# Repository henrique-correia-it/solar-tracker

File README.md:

# Dual-Axis IoT Solar Tracker

**Bare-metal ATmega328P firmware with PID control, an ESP8266 IoT gateway (MQTT + ThingSpeak), a custom KiCad PCB and a real-time web dashboard.**

> Academic team project for the LABSI (Systems Laboratory) course, BSc in Electrical and Computer Engineering, ISEP, 2025/2026.
> **Authors:** Henrique Correia and Gonçalo Teixeira.

🌐 **Project website (live):** <http://ave.dee.isep.ipp.pt/~1221309/LABSI_site/>

| Prototype | Electronics | Wiring |
|---|---|---|
|  |  |  |

## What it does

- Tracks the sun on two axes (pan/tilt) using four LDRs in a quadrant layout and two servomotors.
- Runs a **PID controller per axis** with smoothing, dead-band, integral clamping and a per-cycle step limit, with stronger tolerance under very bright light.
- Uses a **state machine** with automatic, manual, pause and night modes, including a parking position at night.
- Monitors **solar panel voltage, current and power** (INA219 over I2C) and **temperature and humidity** (DHT22, decoded by a non-blocking state machine on Timer2).
- Publishes telemetry in real time over **MQTT** and stores history on **ThingSpeak**. The dashboard can also send remote commands.

## Architecture

```text
4x LDR ──ADC──┐
INA219 ──I2C──┤                       ┌── MQTT (HiveMQ) ── WebSockets ──► Web dashboard (live)
DHT22 ─1-Wire─┼─► ATmega328P ──UART──► ESP8266 ─┤
Button ──INT──┤      │                          └── HTTP ── ThingSpeak ──► Web dashboard (history)
              │      └── Fast PWM 50 Hz ──► 2x servos
              └─ (legacy) HC-05 Bluetooth ──► Python desktop app
```

Detailed Mermaid flowcharts (main loop, interrupts, PID, DHT22 state machine, ESP8266, Python app) are in [docs/architecture.md](docs/architecture.md).

## Technical highlights

**ATmega328P firmware** ([firmware/atmega328p/main.c](firmware/atmega328p/main.c)): register-level C with no Arduino libraries.

- Timers and interrupts: a millisecond system tick, a debounced external button interrupt, and a **watchdog**.
- ADC sampling of the four LDRs with per-sensor calibration and exponential smoothing.
- Fast PWM at 50 Hz on Timer1 driving the two servos.
- I2C (TWI) driver with timeouts for the INA219.
- DHT22 protocol decoded without blocking delays.
- Non-blocking UART with a formatted telemetry protocol to the gateway.

**ESP8266 gateway** ([firmware/esp8266/esp8266.ino](firmware/esp8266/esp8266.ino)):

- Wi-Fi multi-network connection.
- MQTT publish/subscribe with JSON payloads (PubSubClient, ArduinoJson).
- NTP time synchronisation with the Portuguese timezone.
- Periodic ThingSpeak uploads and status LEDs.

**Hardware** ([hardware/](hardware/)):

- KiCad schematic and PCB with fabrication files (BOM, positions, netlist, Gerber archive).
- 3D-printable STL parts for the tracker structure.

**Web dashboard** ([dashboard/](dashboard/)):

- HTML, CSS and JavaScript with Chart.js.
- Live MQTT data over WebSockets and ThingSpeak history with date filters.
- Remote manual control.
- Engineering documentation pages with a 3D PCB model.

**Python bridge** ([bridge/app_ponte.py](bridge/app_ponte.py)):

- Desktop app (ttkbootstrap) used by the earlier Bluetooth (HC-05/BLE) version.
- Shows live sensor data and forwards it to ThingSpeak.

## Repository layout

```text
firmware/atmega328p/   bare-metal C firmware (ATmega328P @ 16 MHz)
firmware/esp8266/      Wi-Fi/MQTT/ThingSpeak gateway (Arduino core for ESP8266)
dashboard/             web dashboard and project website
bridge/                Python desktop bridge (Bluetooth -> ThingSpeak)
hardware/kicad/        schematic, PCB and production files
hardware/3d-models/    printable structure parts (STL)
docs/                  architecture and flowcharts, images
```

## Building and running

**ATmega328P**

1. Build `firmware/atmega328p/main.c` with `avr-gcc` (or Microchip Studio) for the `atmega328p` at `F_CPU=16000000UL`.
2. Flash it with a USBasp or another ISP programmer.

**ESP8266**

1. Copy `firmware/esp8266/secrets.example.h` to `secrets.h` and fill in your Wi-Fi network and ThingSpeak write key. `secrets.h` is ignored by Git.
2. Install the `PubSubClient` and `ArduinoJson` libraries.
3. Flash with the Arduino IDE (ESP8266 core).

**Dashboard**

1. Set your ThingSpeak channel and read key in `TS_CONFIG` at the top of `dashboard/script.js`.
2. Open `dashboard/index.html`, or serve the folder with any static server.

**Python bridge**

```bash
pip install -r bridge/requirements.txt
THINGSPEAK_WRITE_KEY=... python bridge/app_ponte.py
```

> Credentials are not part of this repository. Configure your own Wi-Fi network, ThingSpeak channel and keys before running.
> The dashboard's admin lock is a client-side demo only, not real authentication.

## Team

- **Henrique Correia**
- **Gonçalo Teixeira**

ISEP — Department of Electrical Engineering.

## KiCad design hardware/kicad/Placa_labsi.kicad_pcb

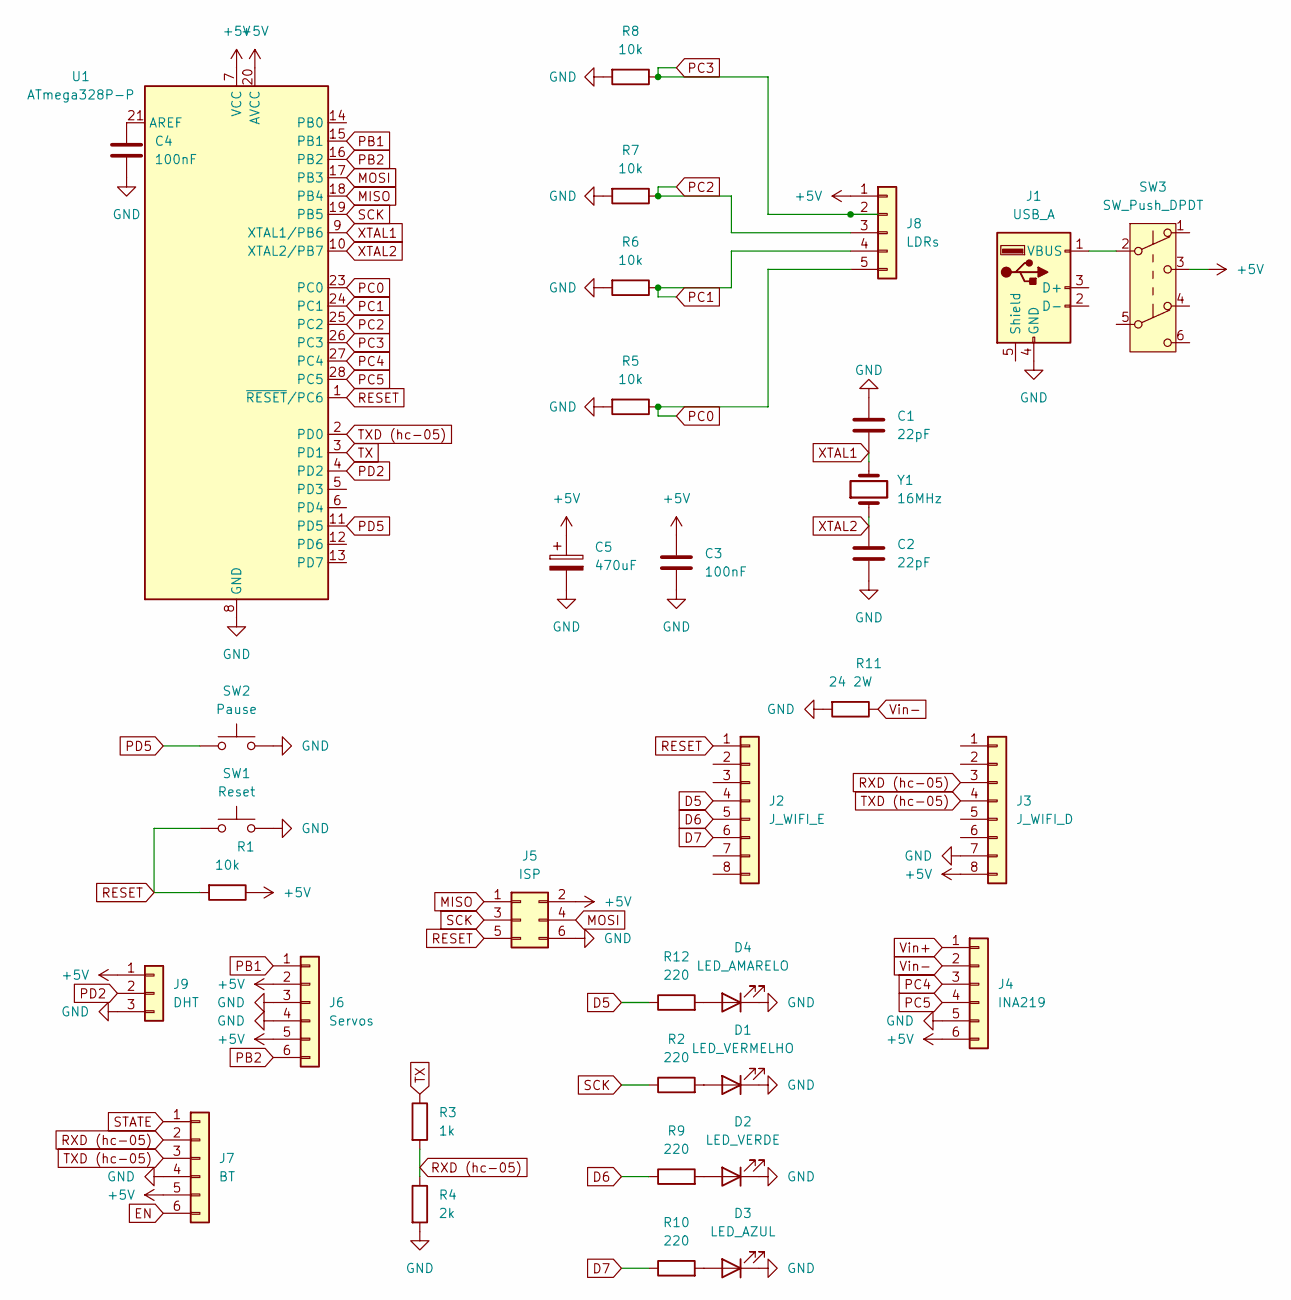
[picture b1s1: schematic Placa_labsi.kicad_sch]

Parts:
C1, C2: 22pF; C_Disc_D5.0mm_W2.5mm_P2.50mm
C3, C4: 100nF; C_Disc_D5.0mm_W2.5mm_P2.50mm
C5: 470uF; CP_Radial_D6.3mm_P2.50mm
D1: LED_VERMELHO; LED_D5.0mm
D2: LED_VERDE; LED_D5.0mm
D3: LED_AZUL; LED_D5.0mm
D4: LED_AMARELO; LED_D5.0mm
J1: USB_A; USB_A_Molex_67643_Horizontal
J2: J_WIFI_E; PinSocket_1x08_P2.54mm_Vertical
J3: J_WIFI_D; PinSocket_1x08_P2.54mm_Vertical
J4: INA219; PinSocket_1x06_P2.54mm_Vertical
J5: ISP; IDC-Header_2x03_P2.54mm_Vertical
J6: Servos; PinSocket_1x06_P2.54mm_Vertical
J7: BT; PinSocket_1x06_P2.54mm_Vertical
J8: LDRs; PinSocket_1x05_P2.54mm_Vertical
J9: DHT; PinSocket_1x03_P2.54mm_Vertical
R1, R5, R6, R7, R8: 10k; R_Axial_DIN0207_L6.3mm_D2.5mm_P7.62mm_Horizontal
R2, R9, R10, R12: 220; R_Axial_DIN0207_L6.3mm_D2.5mm_P7.62mm_Horizontal
R3: 1k; R_Axial_DIN0207_L6.3mm_D2.5mm_P7.62mm_Horizontal
R4: 2k; R_Axial_DIN0207_L6.3mm_D2.5mm_P7.62mm_Horizontal
R11: 24 2W; R_Axial_DIN0414_L11.9mm_D4.5mm_P15.24mm_Horizontal
SW1: Reset; SW_PUSH_6mm
SW2: Pause; SW_PUSH_6mm
SW3: SW_Push_DPDT; SW_CK_JS202011CQN_DPDT_Straight
U1: ATmega328P-P; DIP-28_W7.62mm_Socket
Y1: 16MHz; Crystal_HC49-U_Vertical

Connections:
+5V: C3.1, C5.1, J3.8, J4.6, J5.2, J6.2, J6.5, J7.5, J8.1, J9.1, R1.1, SW3.3 (C), U1.7 (VCC), U1.20 (AVCC)
D5: J2.4, R12.1
D6: J2.5, R9.1
D7: J2.6, R10.1
EN: J7.6
GND: C1.1, C2.2, C3.2, C4.2, C5.2, D1.1 (K), D2.1 (K), D3.1 (K), D4.1 (K), J1.4 (GND), J3.7, J4.5, J5.6, J6.3, J6.4, J7.4, J9.3, R4.2, R5.2, R6.2, R7.2, R8.2, R11.2, SW1.2, SW2.2, U1.8 (GND), U1.22 (GND)
MISO: J5.1, U1.18 (PB4)
MOSI: J5.4, U1.17 (PB3)
unnamed: D1.2 (A), R2.2
unnamed: D2.2 (A), R9.2
unnamed: D3.2 (A), R10.2
unnamed: D4.2 (A), R12.2
unnamed: J1.1 (VBUS), SW3.2 (B)
unnamed: C4.1, U1.21 (AREF)
PB1: J6.1, U1.15 (PB1)
PB2: J6.6, U1.16 (PB2)
PC0: J8.5, R5.1, U1.23 (PC0)
PC1: J8.4, R6.1, U1.24 (PC1)
PC2: J8.3, R7.1, U1.25 (PC2)
PC3: J8.2, R8.1, U1.26 (PC3)
PC4: J4.3, U1.27 (PC4)
PC5: J4.4, U1.28 (PC5)
PD2: J9.2, U1.4 (PD2)
PD5: SW2.1, U1.11 (PD5)
RESET: J2.1, J5.5, R1.2, SW1.1, U1.1 (~RESET/PC6)
RXD (hc-05): J3.3, J7.2, R3.2, R4.1
SCK: J5.3, R2.1, U1.19 (PB5)
STATE: J7.1
TX: R3.1, U1.3 (PD1)
TXD (hc-05): J3.4, J7.3, U1.2 (PD0)
Vin+: J4.1
Vin-: J4.2, R11.1
XTAL1: C1.2, U1.9 (XTAL1/PB6), Y1.2
XTAL2: C2.1, U1.10 (XTAL2/PB7), Y1.1

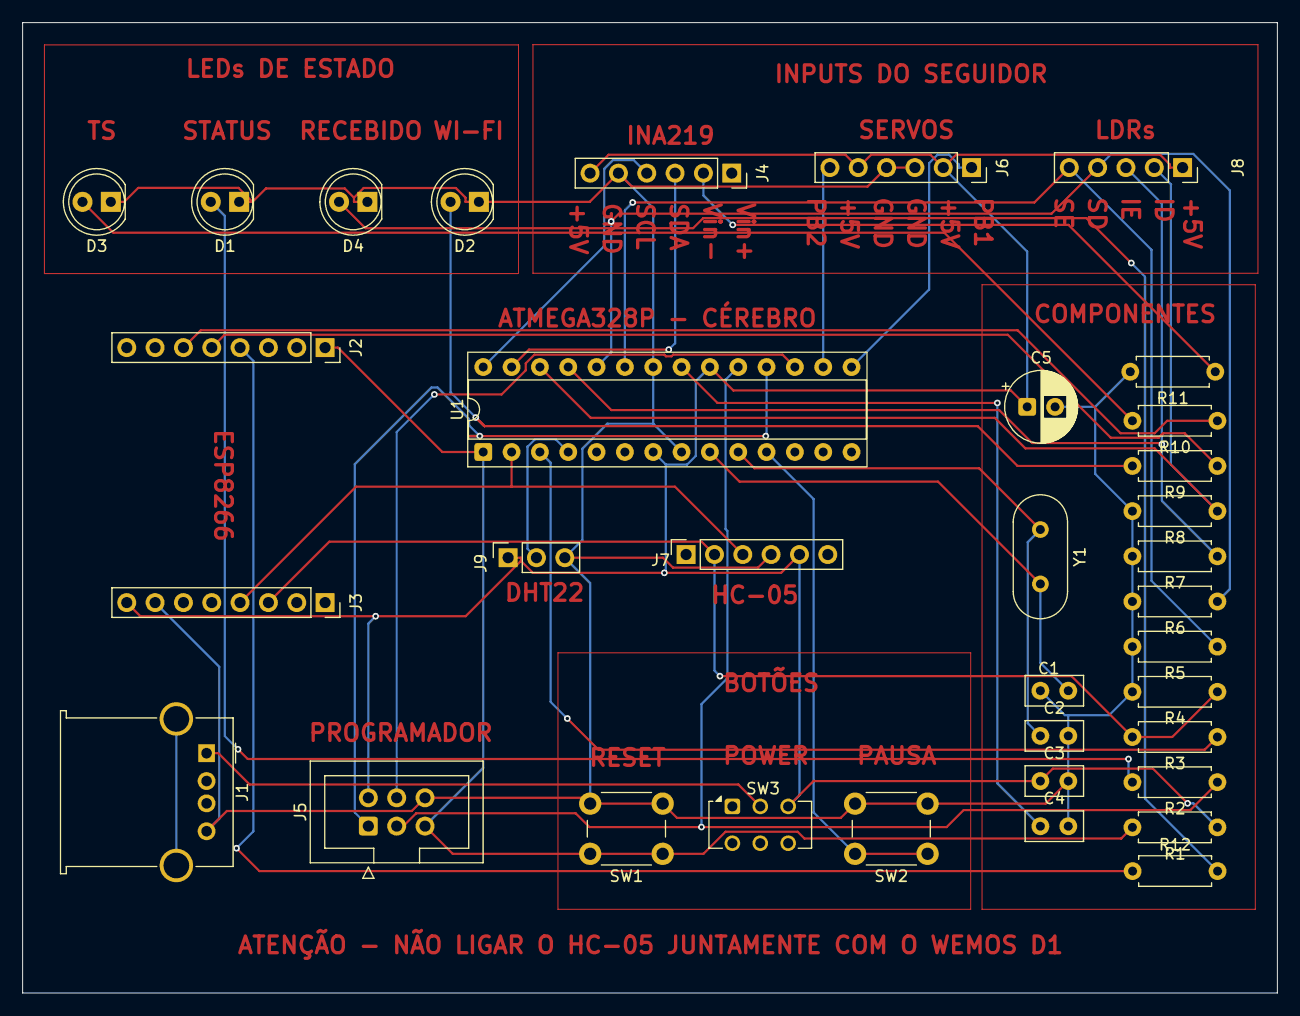
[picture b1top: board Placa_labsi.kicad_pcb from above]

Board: 2 copper layers, 112.5 x 87.0 mm, 35 parts (0 on the bottom side), 31 nets.

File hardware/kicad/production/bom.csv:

Designator,Footprint,Quantity,Value,LCSC Part #
"C1, C2",C_Disc_D5.0mm_W2.5mm_P2.50mm,2,22pF,
"C3, C4",C_Disc_D5.0mm_W2.5mm_P2.50mm,2,100nF,
D1,LED_D5.0mm,1,Status,
J1,USB_A_Molex_67643_Horizontal,1,USB_A,
J5,IDC-Header_2x03_P2.54mm_Vertical,1,ISP,
J6,PinSocket_1x06_P2.54mm_Vertical,1,Servos,
J7,PinSocket_1x06_P2.54mm_Vertical,1,BT,
J8,PinSocket_1x05_P2.54mm_Vertical,1,LDRs,
J9,PinSocket_1x03_P2.54mm_Vertical,1,DHT,
"R1, R2, R5, R6, R7, R8",R_Axial_DIN0207_L6.3mm_D2.5mm_P7.62mm_Horizontal,6,10k,
R3,R_Axial_DIN0207_L6.3mm_D2.5mm_P7.62mm_Horizontal,1,1k,
R4,R_Axial_DIN0207_L6.3mm_D2.5mm_P7.62mm_Horizontal,1,2k,
SW1,SW_PUSH_6mm,1,Reset,
U1,DIP-28_W7.62mm,1,ATmega328P-P,
Y1,Crystal_HC49-U_Vertical,1,16MHz,
